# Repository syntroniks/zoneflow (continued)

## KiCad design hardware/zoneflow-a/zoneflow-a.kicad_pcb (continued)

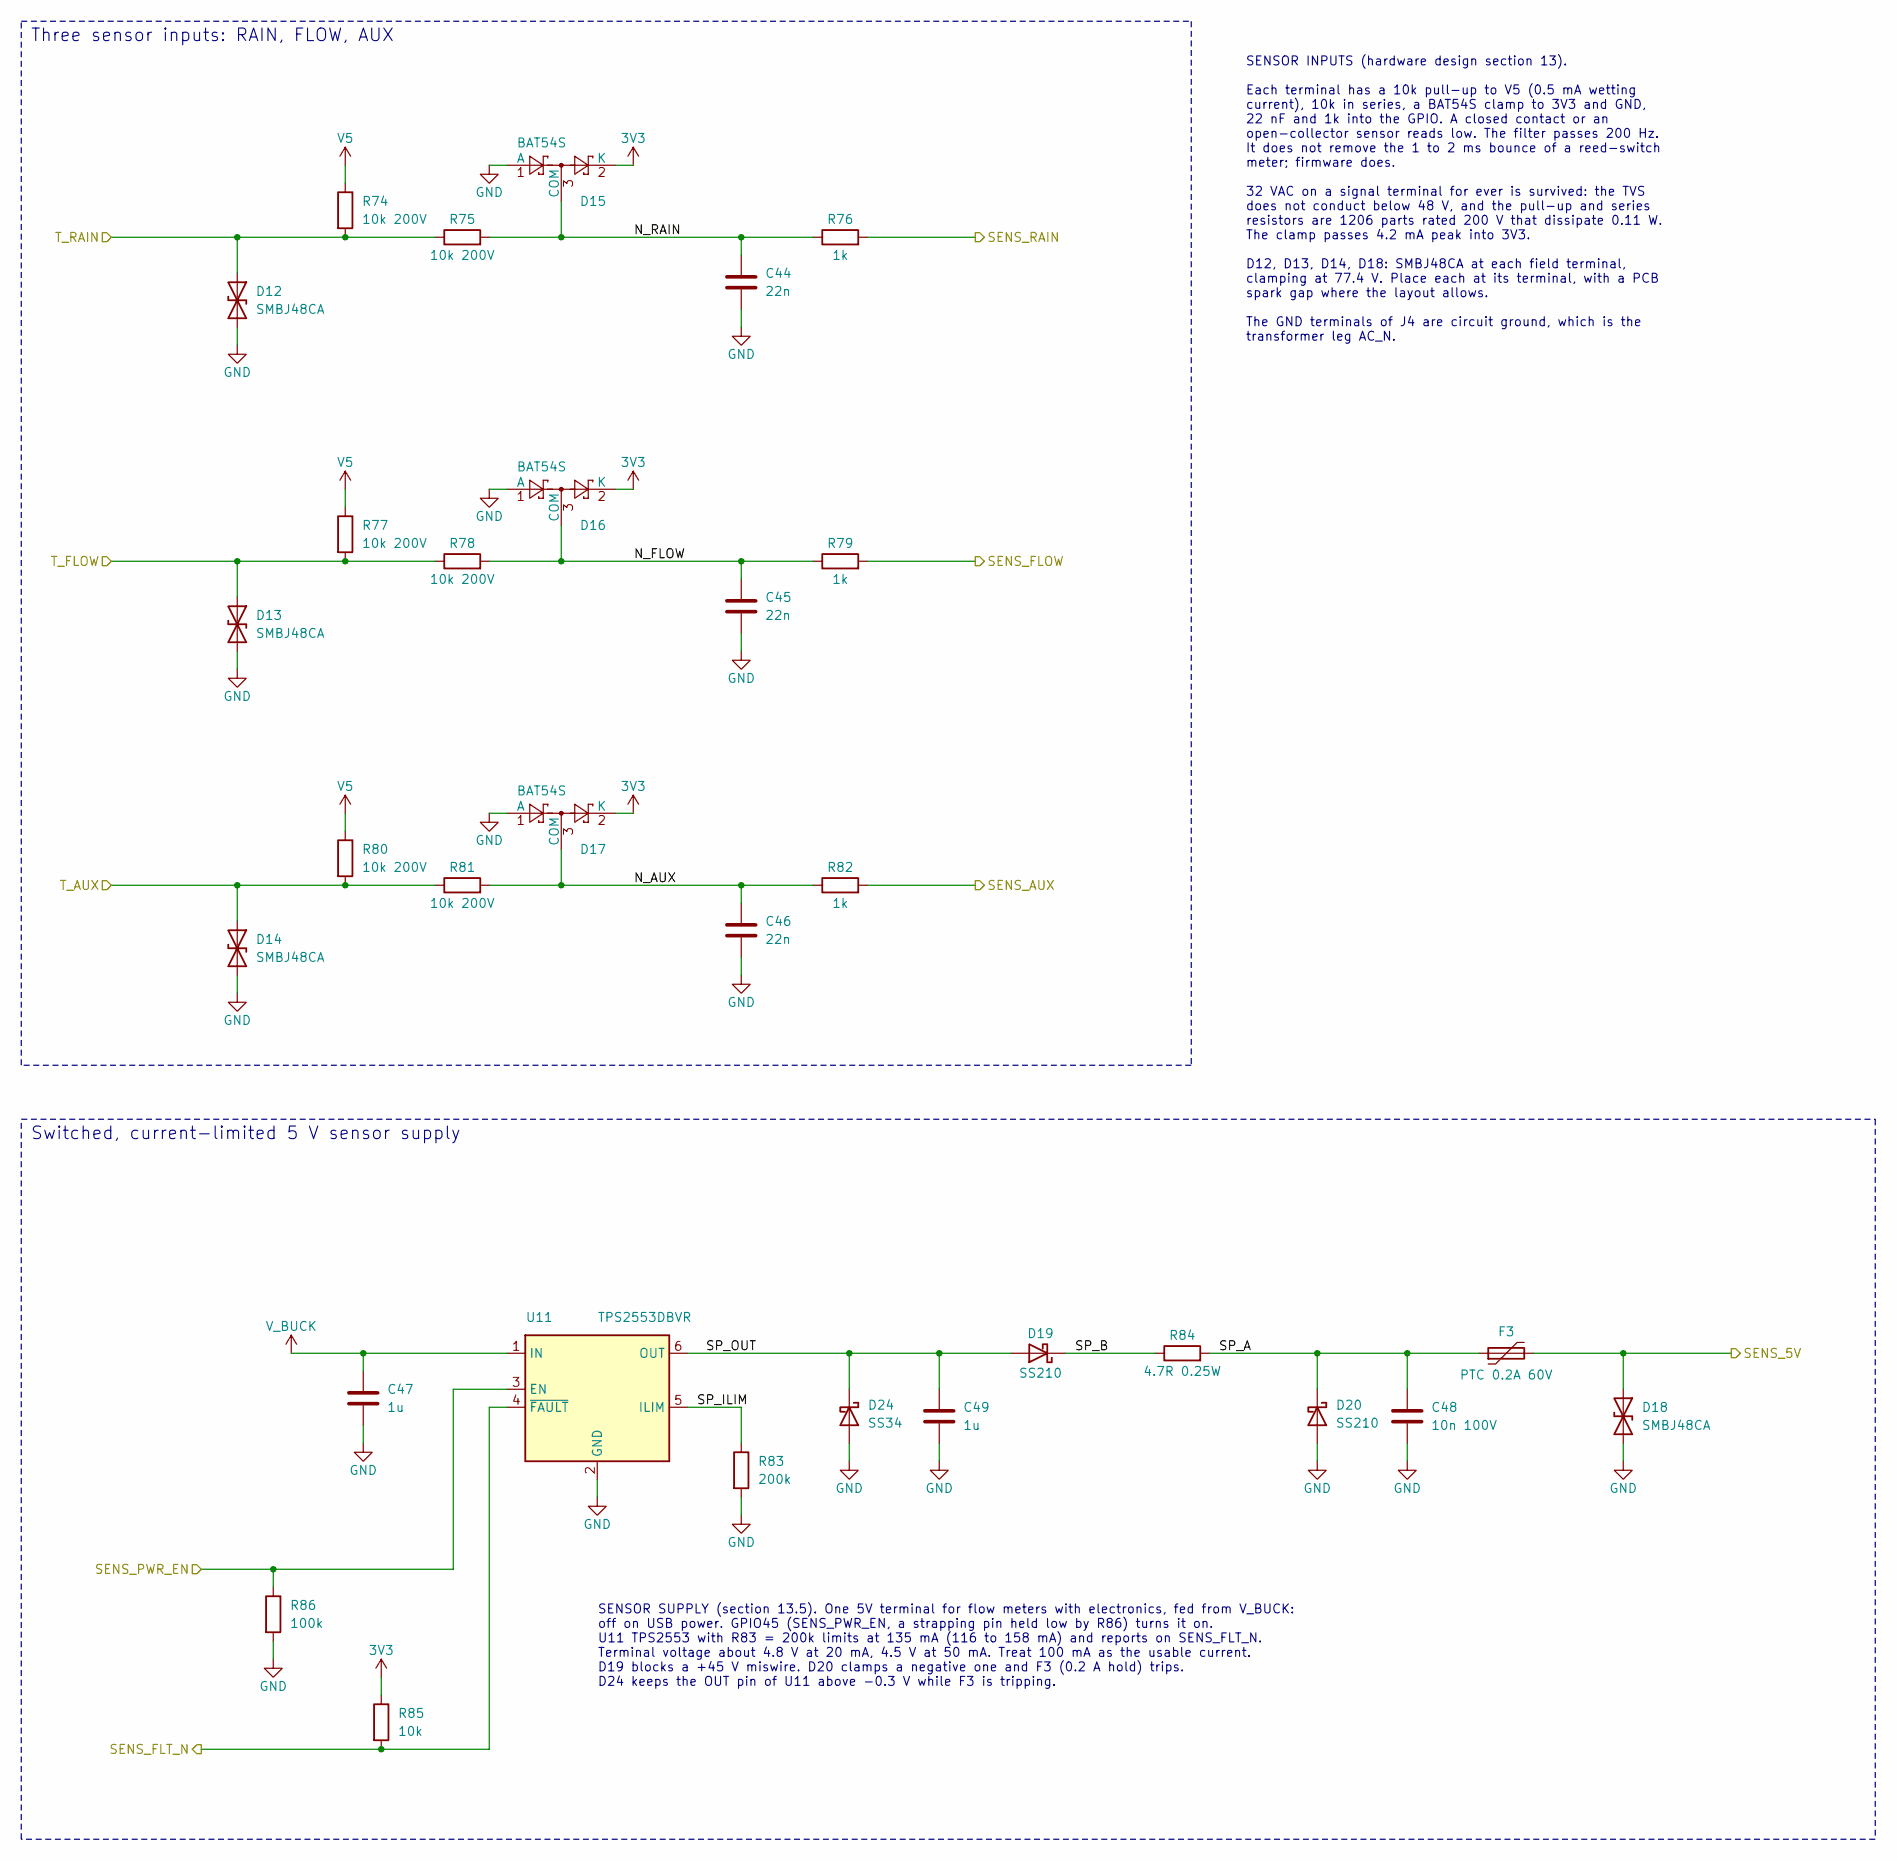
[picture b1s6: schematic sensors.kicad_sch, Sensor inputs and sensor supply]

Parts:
C44, C45, C46: 22n; C_0603_1608Metric; MPN CL10B223KB8NNNC; LCSC C21122
C47, C49: 1u; C_0603_1608Metric; MPN CL10A105KB8NNNC; LCSC C15849
C48: 10n 100V; C_0805_2012Metric; MPN CL21B103KCANNNC; LCSC C18741
D12, D13, D14, D18: SMBJ48CA; D_SMB; MPN SMBJ48CA; LCSC C151264
D15, D16, D17: BAT54S; SOT-23; MPN BAT54S; LCSC C7420333
D19, D20: SS210; D_SMA; MPN SS210; LCSC C14996
D24: SS34; D_SMA; MPN SS34; LCSC C8678
F3: PTC 0.2A 60V; Fuse_1812_4532Metric; MPN 1812L020/60DR; LCSC C315900
R74, R75, R77, R78, R80, R81: 10k 200V; R_1206_3216Metric; MPN 1206W4F1002T5E; LCSC C17902
R76, R79, R82: 1k; R_0603_1608Metric; MPN 0603WAF1001T5E; LCSC C21190
R83: 200k; R_0603_1608Metric; MPN 0603WAF2003T5E; LCSC C25811
R84: 4.7R 0.25W; R_1206_3216Metric; MPN 1206W4F470KT5E; LCSC C17937
R85: 10k; R_0603_1608Metric; MPN 0603WAF1002T5E; LCSC C25804
R86: 100k; R_0603_1608Metric; MPN 0603WAF1003T5E; LCSC C25803
U11: TPS2553DBVR; SOT-23-6; MPN TPS2553DBVR; LCSC C55266

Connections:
3V3: D15.2 (K), D16.2 (K), D17.2 (K), R85.1; also elsewhere on the board
/SENS_5V: D18.1 (A1), F3.2; also elsewhere on the board
/SENS_AUX: R82.2; also elsewhere on the board
/SENS_FLOW: R79.2; also elsewhere on the board
/SENS_FLT_N: R85.2, U11.4 (~FAULT); also elsewhere on the board
/SENS_PWR_EN: R86.1, U11.3 (EN); also elsewhere on the board
/SENS_RAIN: R76.2; also elsewhere on the board
/Sensors/N_AUX: C46.1, D17.3 (COM), R81.2, R82.1
/Sensors/N_FLOW: C45.1, D16.3 (COM), R78.2, R79.1
/Sensors/N_RAIN: C44.1, D15.3 (COM), R75.2, R76.1
/Sensors/SP_A: C48.1, D20.1 (K), F3.1, R84.2
/Sensors/SP_B: D19.1 (K), R84.1
/Sensors/SP_ILIM: R83.1, U11.5 (ILIM)
/Sensors/SP_OUT: C49.1, D19.2 (A), D24.1 (K), U11.6 (OUT)
/T_AUX: D14.1 (A1), R80.2, R81.1; also elsewhere on the board
/T_FLOW: D13.1 (A1), R77.2, R78.1; also elsewhere on the board
/T_RAIN: D12.1 (A1), R74.2, R75.1; also elsewhere on the board
GND: C44.2, C45.2, C46.2, C47.2, C48.2, C49.2, D12.2 (A2), D13.2 (A2), D14.2 (A2), D15.1 (A), D16.1 (A), D17.1 (A), D18.2 (A2), D20.2 (A), D24.2 (A), R83.2, R86.2, U11.2 (GND); also elsewhere on the board
V5: R74.1, R77.1, R80.1; also elsewhere on the board
V_BUCK: C47.1, U11.1 (IN); also elsewhere on the board

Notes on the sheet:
Three sensor inputs: RAIN, FLOW, AUX
Switched, current-limited 5 V sensor supply
SENSOR SUPPLY (section 13.5). One 5V terminal for flow meters with electronics, fed from V_BUCK: off on USB power. GPIO45 (SENS_PWR_EN, a strapping pin held low by R86) turns it on. U11 TPS2553 with R83 = 200k limits at 135 mA (116 to 158 mA) and reports on SENS_FLT_N. Terminal voltage about 4.8 V 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
SENSOR INPUTS (hardware design section 13). Each terminal has a 10k pull-up to V5 (0.5 mA wetting current), 10k in series, a BAT54S clamp to 3V3 and GND, 22 nF and 1k into the GPIO. A closed contact or an open-collector sensor reads low. The filter passes 200 Hz. It does not remove the 1 to 2 ms bo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

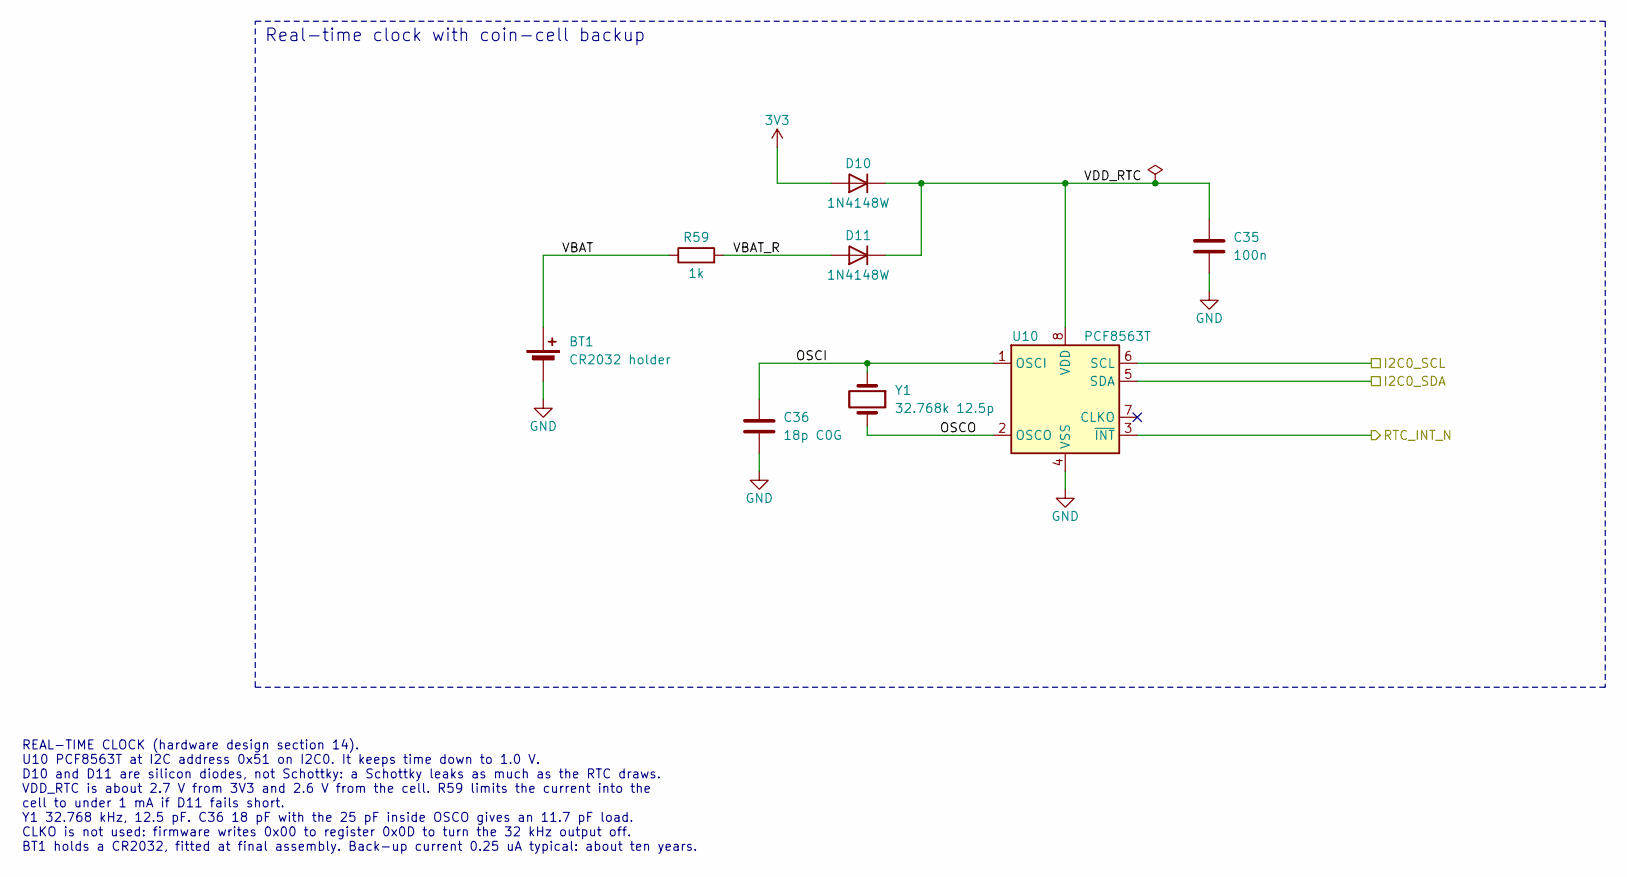
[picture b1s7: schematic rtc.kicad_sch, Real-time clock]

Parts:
BT1: CR2032 holder; BatteryHolder_QJ_CR2032-BS-6-1; MPN CR2032-BS-6-1; LCSC C70377
C35: 100n; C_0603_1608Metric; MPN CC0603KRX7R9BB104; LCSC C14663
C36: 18p C0G; C_0603_1608Metric; MPN CL10C180JB8NNNC; LCSC C1647
D10, D11: 1N4148W; D_SOD-123; MPN 1N4148W; LCSC C81598
R59: 1k; R_0603_1608Metric; MPN 0603WAF1001T5E; LCSC C21190
U10: PCF8563T; SOIC-8_3.9x4.9mm_P1.27mm; MPN PCF8563T/5,518; LCSC C7440
Y1: 32.768k 12.5p; Crystal_SMD_3215-2Pin_3.2x1.5mm; MPN Q13FC13500004; LCSC C32346

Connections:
3V3: D10.2 (A); also elsewhere on the board
/I2C0_SCL: U10.6 (SCL); also elsewhere on the board
/I2C0_SDA: U10.5 (SDA); also elsewhere on the board
/RTC/OSCI: C36.1, U10.1 (OSCI), Y1.1
/RTC/OSCO: U10.2 (OSCO), Y1.2
/RTC/VBAT: BT1.1 (+), R59.1
/RTC/VBAT_R: D11.2 (A), R59.2
/RTC/VDD_RTC: C35.1, D10.1 (K), D11.1 (K), U10.8 (VDD)
/RTC_INT_N: U10.3 (~INT); also elsewhere on the board
GND: BT1.2 (-), C35.2, C36.2, U10.4 (VSS); also elsewhere on the board

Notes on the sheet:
REAL-TIME CLOCK (hardware design section 14). U10 PCF8563T at I2C address 0x51 on I2C0. It keeps time down to 1.0 V. D10 and D11 are silicon diodes, not Schottky: a Schottky leaks as much as the RTC draws. VDD_RTC is about 2.7 V from 3V3 and 2.6 V from the cell. R59 limits the current into the cell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
Real-time clock with coin-cell backup

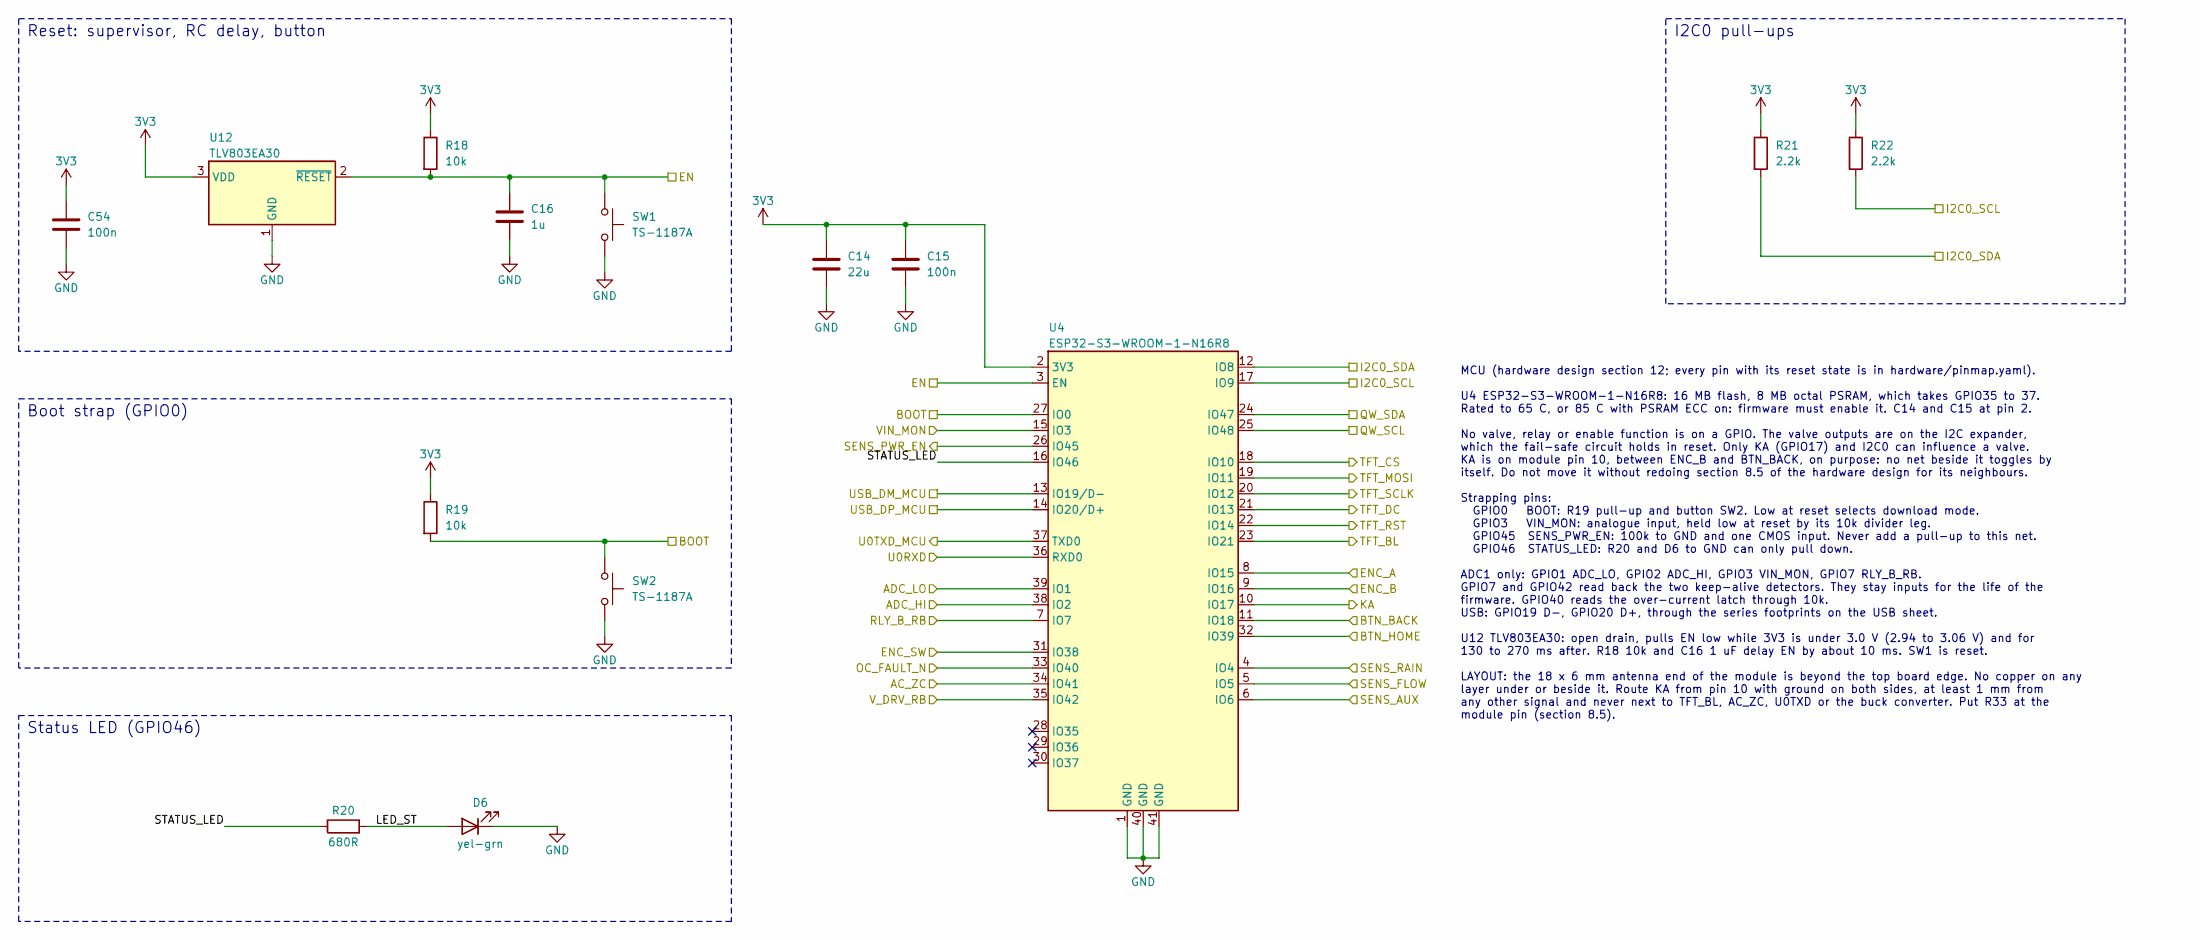
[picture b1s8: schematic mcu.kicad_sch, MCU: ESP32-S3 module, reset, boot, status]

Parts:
C14: 22u; C_1206_3216Metric; MPN CL31A226KAHNNNE; LCSC C12891
C15, C54: 100n; C_0603_1608Metric; MPN CC0603KRX7R9BB104; LCSC C14663
C16: 1u; C_0603_1608Metric; MPN CL10A105KB8NNNC; LCSC C15849
D6: yel-grn; LED_0603_1608Metric; MPN LTST-C190KGKT; LCSC C125094
R18, R19: 10k; R_0603_1608Metric; MPN 0603WAF1002T5E; LCSC C25804
R20: 680R; R_0603_1608Metric; MPN 0603WAF6800T5E; LCSC C23228
R21, R22: 2.2k; R_0603_1608Metric; MPN 0603WAF2201T5E; LCSC C4190
SW1, SW2: TS-1187A; SW_Push_1P1T_XKB_TS-1187A; MPN TS-1187A-B-A-B; LCSC C318884
U4: ESP32-S3-WROOM-1-N16R8; ESP32-S3-WROOM-1; MPN ESP32-S3-WROOM-1-N16R8; LCSC C2913202
U12: TLV803EA30; SOT-23; MPN TLV803EA30DBZR; LCSC C5218924

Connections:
3V3: C14.1, C15.1, C54.1, R18.1, R19.1, R21.1, R22.1, U4.2 (3V3), U12.3 (VDD); also elsewhere on the board
/AC_ZC: U4.34 (IO41); also elsewhere on the board
/ADC_HI: U4.38 (IO2); also elsewhere on the board
/ADC_LO: U4.39 (IO1); also elsewhere on the board
/BOOT: R19.2, SW2.1, U4.27 (IO0); also elsewhere on the board
/BTN_BACK: U4.11 (IO18); also elsewhere on the board
/BTN_HOME: U4.32 (IO39); also elsewhere on the board
/EN: C16.1, R18.2, SW1.1, U4.3 (EN), U12.2 (~RESET); also elsewhere on the board
/ENC_A: U4.8 (IO15); also elsewhere on the board
/ENC_B: U4.9 (IO16); also elsewhere on the board
/ENC_SW: U4.31 (IO38); also elsewhere on the board
/I2C0_SCL: R22.2, U4.17 (IO9); also elsewhere on the board
/I2C0_SDA: R21.2, U4.12 (IO8); also elsewhere on the board
/KA: U4.10 (IO17); also elsewhere on the board
/MCU/LED_ST: D6.2 (A), R20.2
/MCU/STATUS_LED: R20.1, U4.16 (IO46)
/OC_FAULT_N: U4.33 (IO40); also elsewhere on the board
/QW_SCL: U4.25 (IO48); also elsewhere on the board
/QW_SDA: U4.24 (IO47); also elsewhere on the board
/RLY_B_RB: U4.7 (IO7); also elsewhere on the board
/SENS_AUX: U4.6 (IO6); also elsewhere on the board
/SENS_FLOW: U4.5 (IO5); also elsewhere on the board
/SENS_PWR_EN: U4.26 (IO45); also elsewhere on the board
/SENS_RAIN: U4.4 (IO4); also elsewhere on the board
/TFT_BL: U4.23 (IO21); also elsewhere on the board
/TFT_CS: U4.18 (IO10); also elsewhere on the board
/TFT_DC: U4.21 (IO13); also elsewhere on the board
/TFT_MOSI: U4.19 (IO11); also elsewhere on the board
/TFT_RST: U4.22 (IO14); also elsewhere on the board
/TFT_SCLK: U4.20 (IO12); also elsewhere on the board
/U0RXD: U4.36 (RXD0); also elsewhere on the board
/U0TXD_MCU: U4.37 (TXD0); also elsewhere on the board
/USB_DM_MCU: U4.13 (IO19/D-); also elsewhere on the board
/USB_DP_MCU: U4.14 (IO20/D+); also elsewhere on the board
/VIN_MON: U4.15 (IO3); also elsewhere on the board
/V_DRV_RB: U4.35 (IO42); also elsewhere on the board
GND: C14.2, C15.2, C16.2, C54.2, D6.1 (K), SW1.2, SW2.2, U4.1 (GND), U4.40 (GND), U4.41 (GND), U12.1 (GND); also elsewhere on the board

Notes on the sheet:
Reset: supervisor, RC delay, button
Boot strap (GPIO0)
Status LED (GPIO46)
I2C0 pull-ups
MCU (hardware design section 12; every pin with its reset state is in hardware/pinmap.yaml). U4 ESP32-S3-WROOM-1-N16R8: 16 MB flash, 8 MB octal PSRAM, which takes GPIO35 to 37. Rated to 65 C, or 85 C with PSRAM ECC on: firmware must enable it. C14 and C15 at pin 2. No valve, relay or enable functio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

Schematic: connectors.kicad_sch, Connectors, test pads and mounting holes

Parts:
C17: 100n; C_0603_1608Metric; MPN CC0603KRX7R9BB104; LCSC C14663
F2: PTC 0.125A; Fuse_1206_3216Metric; MPN 1206L012WR; LCSC C151160
H1: A: 5.5, 105; MountingHole_3.4mm_M3_Keepout9mm
H2: B: 75, 106; MountingHole_3.4mm_M3_Keepout9mm
H3: C: 4.5, 12; MountingHole_3.4mm_M3_Keepout7mm
H4: D: 109.5, 12; MountingHole_3.4mm_M3_Keepout7mm
J1: 24VAC; KF2EDGR-3.81-2P; MPN KF2EDGR-3.81-2P; LCSC C441182
J2, J4: KF2EDGR-3.81-7P; MPN KF2EDGR-3.81-7P; LCSC C441187
J3: KF2EDGR-3.81-4P; MPN KF2EDGR-3.81-4P; LCSC C441184
J6: Qwiic SM04B-SRSS; JST_SH_SM04B-SRSS-TB_1x04-1MP_P1.00mm_Horizontal; MPN SM04B-SRSS-TB(LF)(SN); LCSC C160404
J8: debug 1x6; PinHeader_1x06_P2.54mm_Vertical
R23, R24: 4.7k; R_0603_1608Metric; MPN 0603WAF4701T5E; LCSC C23162
R99: 0R; R_0603_1608Metric; MPN 0603WAF0000T5E; LCSC C21189
TP1, TP2, TP3, TP4, TP5, TP6, TP7, TP8, TP9, TP10, TP11, TP12, TP13, TP14, TP15, TP16, TP17, TP18, TP19, TP20, TP21, TP22, TP23, TP24, TP25, TP26, TP27, TP28, TP29, TP30: TP; TestPoint_Pad_D1.5mm
U9: USBLC6-2SC6; SOT-23-6; MPN USBLC6-2SC6; LCSC C7519

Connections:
3V3: F2.1, J8.1, R23.1, R24.1, TP4.1; also elsewhere on the board
/AC_L_IN: J1.1; also elsewhere on the board
/AC_N: J1.2; also elsewhere on the board
/AC_ZC: TP16.1; also elsewhere on the board
/BOOT: J8.6; also elsewhere on the board
/COM: J2.1, J2.2, TP22.1; also elsewhere on the board
/Connectors/QW_3V3: C17.1, F2.2, J6.2, U9.5 (VBUS)
/Connectors/U0TXD: J8.3, R99.2
/DRV_EN: TP12.1; also elsewhere on the board
/EN: J8.5; also elsewhere on the board
/EXP_INT_N: TP21.1; also elsewhere on the board
/FAULT: TP11.1; also elsewhere on the board
/I2C0_SCL: TP19.1; also elsewhere on the board
/I2C0_SDA: TP18.1; also elsewhere on the board
/ISENSE_HI: TP14.1; also elsewhere on the board
/ISENSE_LO: TP13.1; also elsewhere on the board
/ISNS: TP17.1; also elsewhere on the board
/KA_N2: TP8.1; also elsewhere on the board
/KA_OK: TP9.1; also elsewhere on the board
/OC_TRIP_N: TP10.1; also elsewhere on the board
/OUT_MV: J2.3; also elsewhere on the board
/OUT_Z1: J2.4; also elsewhere on the board
/OUT_Z2: J2.5; also elsewhere on the board
/OUT_Z3: J2.6; also elsewhere on the board
/OUT_Z4: J2.7; also elsewhere on the board
/OUT_Z5: J3.1; also elsewhere on the board
/OUT_Z6: J3.2; also elsewhere on the board
/OUT_Z7: J3.3; also elsewhere on the board
/OUT_Z8: J3.4; also elsewhere on the board
/P06: TP26.1; also elsewhere on the board
/P07: TP27.1; also elsewhere on the board
/P16: TP28.1; also elsewhere on the board
/P17: TP29.1; also elsewhere on the board
/PGOOD: TP20.1; also elsewhere on the board
/QW_SCL: J6.4, R24.2, U9.3 (I/O2), U9.4 (I/O2); also elsewhere on the board
/QW_SDA: J6.3, R23.2, U9.1 (I/O1), U9.6 (I/O1); also elsewhere on the board
/RLY_B: TP24.1; also elsewhere on the board
/RTC_INT_N: TP23.1; also elsewhere on the board
/SENS_5V: J4.1, TP30.1; also elsewhere on the board
/SENS_PWR_EN: TP25.1; also elsewhere on the board
/T_AUX: J4.6; also elsewhere on the board
/T_FLOW: J4.2; also elsewhere on the board
/T_RAIN: J4.4; also elsewhere on the board
/U0RXD: J8.4; also elsewhere on the board
/U0TXD_MCU: R99.1; also elsewhere on the board
/VB: TP15.1; also elsewhere on the board
GND: C17.2, J4.3, J4.5, J4.7, J6.1, J8.2, TP5.1, TP6.1, U9.2 (GND); also elsewhere on the board
V5: TP3.1; also elsewhere on the board
VIN_DC: TP1.1; also elsewhere on the board
V_BUCK: TP2.1; also elsewhere on the board
V_DRV: TP7.1; also elsewhere on the board

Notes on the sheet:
Qwiic expansion port on its own bus, I2C1
Terminal order along the bottom edge, left to right as the installer sees it: J1 24V~ 24V~ transformer; pin 2 (AC_N) becomes circuit GND J2 COM COM MV 1 2 3 4 J3 5 6 7 8 8-zone build only (KiCad variant "4-zone": not fitted) J4 5V FLOW GND RAIN GND AUX GND Headers KF2EDGR-3.81, plugs KF2EDGK-3.81 s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
TEST PADS: 1.5 mm, top side. Ground around TP8. No pad may sit in the fuse well.
Factory and debug header (pads only)
Mounting holes (mechanical contract)
H1 to H4: 3.4 mm holes for M3, at the positions of holes A to D.
Test pads
Field terminals: pluggable 3.81 mm headers
QWIIC (section 16.2). F2 holds 0.125 A at 20 C and 0.08 A at 60 C: the port supplies 80 mA. R23, R24 4.7k. U9 clamps the bus lines; place it at J6. Pin order 1 GND, 2 3V3, 3 SDA, 4 SCL.

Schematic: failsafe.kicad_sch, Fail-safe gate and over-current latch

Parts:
C19, C20, C21, C56: 100n; C_0603_1608Metric; MPN CC0603KRX7R9BB104; LCSC C14663
C22: 4.7u; C_0805_2012Metric; MPN CL21A475KAQNNNE; LCSC C1779
C23: 10u; C_0805_2012Metric; MPN CL21A106KAYNNNE; LCSC C15850
C24, C55: 10n; C_0603_1608Metric; MPN 0603B103K500NT; LCSC C57112
C33: 4.7n; C_0603_1608Metric; MPN 0603B472K500NT; LCSC C53987
D7: BAT54S; SOT-23; MPN BAT54S; LCSC C7420333
D8: red; LED_0603_1608Metric; MPN KT-0603R; LCSC C2286
Q3: AO3401A; SOT-23; MPN AO3401A; LCSC C15127
R13: 1M; R_0603_1608Metric; MPN 0603WAF1004T5E; LCSC C22935
R25, R31: 100k; R_0603_1608Metric; MPN 0603WAF1003T5E; LCSC C25803
R26, R35, R36, R52, R53, R87: 10k; R_0603_1608Metric; MPN 0603WAF1002T5E; LCSC C25804
R29: 220R; R_0603_1608Metric; MPN 0603WAF2200T5E; LCSC C22962
R30, R91, R100: 110k; R_0603_1608Metric; MPN 0603WAF1103T5E; LCSC C25805
R32: 510k; R_0603_1608Metric; MPN 0603WAF5103T5E; LCSC C23192
R33: 2.2k; R_0603_1608Metric; MPN 0603WAF2201T5E; LCSC C4190
R34: 15k; R_0603_1608Metric; MPN 0603WAF1502T5E; LCSC C22809
R54: 1k; R_0603_1608Metric; MPN 0603WAF1001T5E; LCSC C21190
R92: 4.7k; R_0603_1608Metric; MPN 0603WAF4701T5E; LCSC C23162
U6: LM2901DR; SOIC-14_3.9x8.7mm_P1.27mm; MPN LM2901DR; LCSC C7932
U7: 74HC132D; SOIC-14_3.9x8.7mm_P1.27mm; MPN 74HC132D,653; LCSC C5601
U13: TPS3701DDCR; TSOT-23-6; MPN TPS3701DDCR; LCSC C132788

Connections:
3V3: C20.1, C56.1, Q3.2 (S), R13.1, R25.1, R34.1, R36.1, R53.1, U7.14 (VCC), U13.5 (VDD); also elsewhere on the board
/DRV_EN: U7.11; also elsewhere on the board
/FAULT: R54.1, U7.3, U7.5; also elsewhere on the board
/Failsafe/DRV_EN_N: Q3.1 (G), R25.2, U7.8, U7.12, U7.13
/Failsafe/FAULT_N: R87.1, U7.2, U7.6, U7.10
/Failsafe/KA_INP: C24.1, R31.2, R32.1, U6.7 (+)
/Failsafe/KA_N0: C22.1, R29.2
/Failsafe/KA_N1: C22.2, D7.3 (COM)
/Failsafe/KA_REF: R34.2, R35.1, U6.6 (-)
/Failsafe/LED_FLT: D8.2 (A), R54.2
/Failsafe/OC_CMP: C33.1, R52.2, U6.4 (-), U6.9 (+)
/Failsafe/OV_DIV: C55.1, R13.2, R100.1, U13.4 (INB)
/ISENSE_LO: R52.1; also elsewhere on the board
/KA: R29.1, R33.1; also elsewhere on the board
/KA_N2: C23.1, D7.2 (K), R30.1, R31.1, R91.1; also elsewhere on the board
/KA_OK: R32.2, R36.2, U6.1, U7.4, U7.9; also elsewhere on the board
/OC_FAULT_N: R87.2; also elsewhere on the board
/OC_TRIP_N: R53.2, U6.2, U6.14, U7.1, U13.6 (~OUTB); also elsewhere on the board
/VH: U6.5 (+); also elsewhere on the board
/VL: U6.8 (-); also elsewhere on the board
/V_DRV_RB: R92.2; also elsewhere on the board
GND: C19.2, C20.2, C21.2, C23.2, C24.2, C33.2, C55.2, C56.2, D7.1 (A), D8.1 (K), R26.2, R30.2, R33.2, R35.2, R91.2, R100.2, U6.12 (V-), U7.7 (GND), U13.2 (GND), U13.3 (INA); also elsewhere on the board
V5: C19.1, U6.3 (V+); also elsewhere on the board
V_DRV: C21.1, Q3.3 (D), R26.1, R92.1; also elsewhere on the board

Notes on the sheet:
LAYOUT (section 8.5): TP8 on KA_N2 keeps ground around it. No pad on KA_N1. Keep this pump (R29, C22, D7) at least 10 mm from the relay pump (R89, C51, D22).
Over-current window comparator on ISENSE_LO
FAIL-SAFE GATE (hardware design section 8) and OVER-CURRENT LATCH (section 9). Detector A. Firmware toggles KA (GPIO17) every 5 ms. It needs an edge at least every 20 ms and no phase shorter than 2.5 ms (the second is for detector B on the expander sheet). Each rising edge pushes charge through C22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
Latch and drive enable
Detector A: keep-alive edges on KA charge C23; U6A compares it with 1.32 V
3V3 over-voltage: U13 holds the set input of the latch low above 4.0 V

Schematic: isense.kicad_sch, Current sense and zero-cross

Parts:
C25, C30, C31: 100n; C_0603_1608Metric; MPN CC0603KRX7R9BB104; LCSC C14663
C26, C27: 1n; C_0603_1608Metric; MPN CL10B102KB8NNNC; LCSC C1588
C28, C29: 330p C0G; C_0603_1608Metric; MPN CL10C331JB8NNNC; LCSC C1664
C32: 1u; C_0603_1608Metric; MPN CL10A105KB8NNNC; LCSC C15849
C34: 10n; C_0603_1608Metric; MPN 0603B103K500NT; LCSC C57112
D9: BAT54S; SOT-23; MPN BAT54S; LCSC C7420333
R37: 0.1R 1% 2W; R_2512_6332Metric; MPN RLP25FEER100; LCSC C160587
R38, R40, R42, R44: 7.5k; R_0603_1608Metric; MPN 0603WAF7501T5E; LCSC C23234
R39, R41, R56, R58, R88: 10k; R_0603_1608Metric; MPN 0603WAF1002T5E; LCSC C25804
R43, R45: 49.9k; R_0603_1608Metric; MPN 0603WAF4992T5E; LCSC C23184
R46, R47, R48: 1k; R_0603_1608Metric; MPN 0603WAF1001T5E; LCSC C21190
R49, R50: 330R; R_0603_1608Metric; MPN 0603WAF3300T5E; LCSC C23138
R51: 100R; R_0603_1608Metric; MPN 0603WAF1000T5E; LCSC C22775
R55: 100k 200V; R_1206_3216Metric; MPN 1206W4F1003T5E; LCSC C17900
R57: 1M; R_0603_1608Metric; MPN 0603WAF1004T5E; LCSC C22935
U6: LM2901DR; SOIC-14_3.9x8.7mm_P1.27mm; MPN LM2901DR; LCSC C7932
U8: MCP6002-I/SN; SOIC-8_3.9x4.9mm_P1.27mm; MPN MCP6002T-I/SN; LCSC C7377

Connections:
3V3: C25.1, D9.2 (K), R48.1, R58.1, U8.8 (V+); also elsewhere on the board
/AC_L: R55.1; also elsewhere on the board
/AC_ZC: R57.2, R58.2, U6.13; also elsewhere on the board
/ADC_HI: C31.1, R47.2; also elsewhere on the board
/ADC_LO: C30.1, R46.2; also elsewhere on the board
/CurrentSense/SA_N: C26.1, R38.2, R39.1, U8.2 (-)
/CurrentSense/SA_P: C27.1, R40.2, R41.1, U8.3 (+)
/CurrentSense/SB_N: C28.1, R42.2, R43.1, U8.6 (-)
/CurrentSense/SB_P: C29.1, R44.2, R45.1, U8.5 (+)
/CurrentSense/ZC_CLAMP: D9.3 (COM), R55.2, R88.1
/CurrentSense/ZC_DIV: C34.1, R56.1, R57.1, R88.2, U6.11 (+)
/ISENSE_HI: C28.2, R43.2, R47.1, U8.7; also elsewhere on the board
/ISENSE_LO: C26.2, R39.2, R46.1, U8.1; also elsewhere on the board
/ISNS: R37.1, R38.1, R42.1; also elsewhere on the board
/VB: C27.2, C29.2, C32.1, R41.2, R45.2, R49.2, R50.1; also elsewhere on the board
/VH: R48.2, R49.1; also elsewhere on the board
/VL: R50.2, R51.1, U6.10 (-); also elsewhere on the board
GND: C25.2, C30.2, C31.2, C32.2, C34.2, D9.1 (A), R37.2, R40.1, R44.1, R51.2, R56.2, U8.4 (V-); also elsewhere on the board

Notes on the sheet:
Bias and trip thresholds
Mains zero-cross and presence detector
CURRENT MEASUREMENT (hardware design section 10). R37 0.1R 1 % 2 W carries the return current of every valve: ISNS is the common T1 node of all triacs. 0.23 W at 1.5 A rms. A 20 A short lifts ISNS to 2.8 V for a half-cycle; the 7.5k input resistors keep that inside the op-amp's 2 mA input limit. U8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
THRESHOLDS (section 9.1). VH 1.425 V, VB 0.806 V, VL 0.188 V: trip at 0.619 V / 0.1333 V/A = 4.64 A peak. ZERO-CROSS (section 11). R55, R88, R56 divide AC_L by 12. D9 clamps; R88 halves the clamped level so the LM2901 input stays above -0.3 V (-0.18 V at -20 C and 32 VAC). U6D compares with VL; R57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
Shunt and two difference amplifiers, both biased at VB

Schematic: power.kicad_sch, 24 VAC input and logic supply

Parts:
C1: 470u 63V; CP_Radial_D12.5mm_L20mm_P5.00mm_LyingDown; MPN 63ZLJ470M12.5X20; LCSC C2940725
C2, C3: 2.2u 100V; C_1210_3225Metric; MPN CL32B225KCJSNNE; LCSC C55151
C4: 2.2n; C_0603_1608Metric; MPN 0603B222K500NT; LCSC C1604
C5, C6: 22u; C_1206_3216Metric; MPN CL31A226KAHNNNE; LCSC C12891
C7: 3.3n; C_0603_1608Metric; MPN CL10B332KB8NNNC; LCSC C1613
C8: 100p C0G; C_0603_1608Metric; MPN CL10C101JB8NNNC; LCSC C14858
C9: 100n; C_0603_1608Metric; MPN CC0603KRX7R9BB104; LCSC C14663
D1: SMCJ48CA; D_SMC; MPN SMCJ48CA; LCSC C41411765
D2: M7; D_SMA; MPN M7; LCSC C95872
D25: SMBJ6.0A; D_SMB; MPN SMBJ6.0A; LCSC C83270
F1, F4: 3A T 0154003.DRT; Fuseholder_Littelfuse_Nano2_154x; MPN 0154003.DRT; LCSC C206913
F5: 0.5A FF 0451.500; Fuse_Littelfuse-NANO2-451_453; MPN 0451.500MRL; LCSC C142836
L1: 47u SRN6045TA; L_Bourns_SRN6045TA; MPN SRN6045TA-470M; LCSC C5151734
R1: 3R 1W surge; R_2512_6332Metric; MPN SR2512JK-073RL; LCSC C2936639
R2: 47k; R_0603_1608Metric; MPN 0603WAF4702T5E; LCSC C25819
R3: 330k; R_0603_1608Metric; MPN 0603WAF3303T5E; LCSC C23137
R4, R10: 10k; R_0603_1608Metric; MPN 0603WAF1002T5E; LCSC C25804
R5: 100k; R_0603_1608Metric; MPN 0603WAF1003T5E; LCSC C25803
R6, R8: 200k; R_0603_1608Metric; MPN 0603WAF2003T5E; LCSC C25811
R7: 1M; R_0603_1608Metric; MPN 0603WAF1004T5E; LCSC C22935
R9: 300k; R_0603_1608Metric; MPN 0603WAF3003T5E; LCSC C23024
U1: LM5164DDAR; TI_SO-PowerPAD-8; MPN LM5164DDAR; LCSC C477928

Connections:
/AC_L: D1.1 (A1), D2.2 (A), F4.2; also elsewhere on the board
/AC_L_IN: F4.1; also elsewhere on the board
/AC_N: F1.1; also elsewhere on the board
/PGOOD: U1.6 (PGOOD); also elsewhere on the board
/Power/BST: C4.1, U1.7 (BST)
/Power/FB: C8.2, R4.2, R5.1, U1.5 (FB)
/Power/FB_MID: R3.2, R4.1
/Power/RIP: C7.1, C8.1, R6.2
/Power/RON: R2.1, U1.4 (RON)
/Power/SW: C4.2, L1.1, R6.1, U1.8 (SW)
/Power/UVLO: R7.2, R8.1, U1.3 (EN/UVLO)
/Power/VIN_U1: C2.1, C3.1, F5.2, U1.2 (VIN)
/Power/VRECT: D2.1 (K), R1.1
/VIN_MON: C9.1, R9.2, R10.1; also elsewhere on the board
GND: C1.2, C2.2, C3.2, C5.2, C6.2, C9.2, D1.2 (A2), D25.2 (A), F1.2, R2.2, R5.2, R8.2, R10.2, U1.1 (GND), U1.9 (EP); also elsewhere on the board
VIN_DC: C1.1, F5.1, R1.2, R7.1, R9.1; also elsewhere on the board
V_BUCK: C5.1, C6.1, C7.2, D25.1 (K), L1.2, R3.1; also elsewhere on the board

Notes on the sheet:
Half-wave rectifier, bulk capacitor, supply monitor
U1 LM5164, 100 V synchronous buck (TI SNVSAU4D). It survives the 77.4 V clamp level. V_BUCK = 1.2 V x (1 + (R3 + R4) / R5) = 5.28 V, 5.16 to 5.40 V over tolerance. R2 47k sets the on-time: 281 kHz. F5, D25 For a switch of U1 that fails short (section 4.8). D25, SMBJ6.0A, holds V_BUCK under 10 V and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
Input fuse, LM5164 buck converter, 5.28 V, over-voltage clamp
24 VAC INPUT AND LOGIC SUPPLY (hardware design section 4). F4, F1 3 A time-lag fuses in holders, one in each transformer leg (section 5.3 says why two). Terminal 2, AC_N, becomes circuit GND behind F1. Both holders sit in the fuse well behind J1. D1 SMCJ48CA: stands off 48 V, above the 45.3 V peak 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
24 VAC input: a fuse in each leg, surge clamp
